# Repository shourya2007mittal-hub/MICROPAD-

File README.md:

# MICROPAD-

I  built a updated macro pad with 9 switches an 0.91 inch Display , a rotor encoder through which I can change between the layers and one RGB LED per switch , It will be  use wireless connection and will use Xiao nrf52840 as the main microcontroller.

## Features

- Base on Xiao NRF Module
- Has per switch LED
- Works wirelessly and has a Battery built in
- Has 9 Switch and 3 Different Layers to switch onto

# Bill of Materials (BOM)

This document contains the list of all components required for the project, including quantities, estimated prices, and direct purchase links.

## Components

| Item | Quantity | Price (USD) | Purchase Link |
|------|----------|------------:|---------------|
| PCB + Shipping | - | 18.72 | https://jlcpcb.com |
| SK6812 Mini-E RGB | 1 Pack | 13.19 | https://www.desertcart.in/products/713547616-50pcs-sk6812-mini-e-rgb-similar-with-ws2812b-sk6812-3228 |
| Mini SPDT Slide Switch (+ Shipping) | Pack of 3 | 1.64 | https://www.amazon.in/gp/product/B0B434R6QF/ref=ox_sc_act_image_1?smid=A2JDRZEGU1IDE2&psc=1 |
| Blank DSA Keycaps | 2 Sets of 5 | 2.00 | https://meckeys.com/shop/accessories/keyboard-accessories/keycaps/blank/blank-dsa-keycaps-1u/ |
| Kailh Hot-Swap Sockets | 2 Packs of 5 | 1.65 | https://meckeys.com/shop/accessories/keyboard-accessories/key-switches/kailh-hot-swap-socket/?attribute_pa_variations=white |
| Gateron Optical Switches | 1 Pack of 10 | 4.50 | https://meckeys.com/shop/accessories/keyboard-accessories/key-switches/gateron-optical-switch-pack/?attribute_pa_key-switches=gateron-optical-silent-brown |
| Meckeys Shipping | - | 1.10 | https://meckeys.com |
| 450mAh 3.7V LiPo Battery | 1 | 1.70 | https://robocraze.com/products/450mah-3-7v-lipo-rechargeable-battery?variant=51440287219936 |
| Rotary Encoder Module | 1 | 0.69 | https://robocraze.com/products/rotary-encoder-module?variant=40193048543385 |
| 0.91" OLED Display Module | 1 | 1.58 | https://robocraze.com/products/0-91-inch-blue-oled-display-module?variant=40194383413401 |
| Seeed Studio XIAO nRF52840 | 1 | 12.16 | https://robocraze.com/products/seeed-studio-xiao-nrf52840-development-board-supports-bluetooth-5-0?variant=47769216516320 |

## Estimated Cost

| Description | Amount (USD) |
|------------|-------------:|
| **Total Estimated Cost** | **58.93** |

### Schematic

###  PCB Design

### 3D Design

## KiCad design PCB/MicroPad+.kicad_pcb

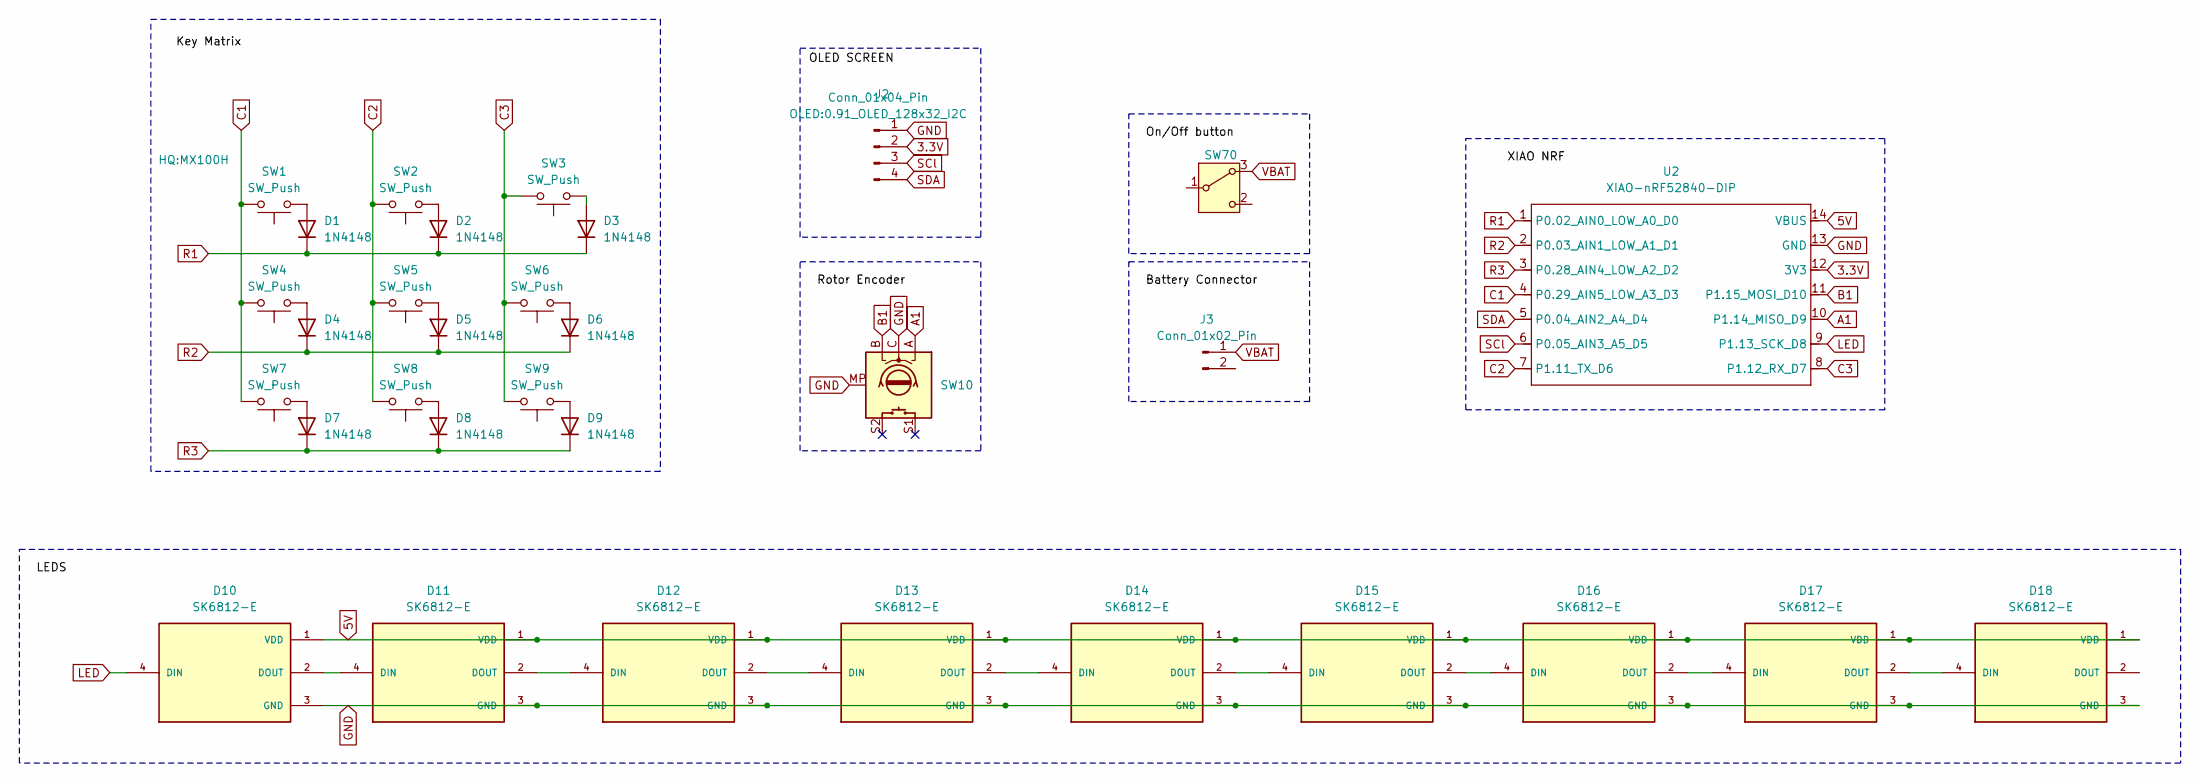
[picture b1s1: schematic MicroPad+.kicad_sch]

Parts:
D1, D2, D3, D4, D5, D6, D7, D8, D9: 1N4148; D_DO-35_SOD27_P7.62mm_Horizontal
D10, D11, D12, D13, D14, D15, D16, D17, D18: SK6812-E; LED_SK6812-E; PARTREV 2
J2: Conn_01x04_Pin; 0.91_OLED_128x32_I2C
J3: Conn_01x02_Pin; AMASS_XT30U-F_1x02_P5.0mm_Vertical
SW1, SW2, SW3, SW4, SW5, SW6, SW7, SW8, SW9: SW_Push; MX100H
SW10: RotaryEncoder_Switch_MP; RotaryEncoder_Alps_EC11E-Switch_Vertical_H20mm
SW70: SW_Wuerth_450301014042; SW_Slide_SPDT_Angled_CK_OS102011MA1Q
U2: XIAO-nRF52840-DIP; XIAO-nRF52840-SMD

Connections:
3.3V: J2.2, U2.12 (3V3)
5V: D10.1 (VDD), D11.1 (VDD), D12.1 (VDD), D13.1 (VDD), D14.1 (VDD), D15.1 (VDD), D16.1 (VDD), D17.1 (VDD), D18.1 (VDD), U2.14 (VBUS)
A1: SW10.A, U2.10 (P1.14_MISO_D9)
B1: SW10.B, U2.11 (P1.15_MOSI_D10)
C1: SW1.2, SW4.2, SW7.2, U2.4 (P0.29_AIN5_LOW_A3_D3)
C2: SW2.2, SW5.2, SW8.2, U2.7 (P1.11_TX_D6)
C3: SW3.2, SW6.2, SW9.2, U2.8 (P1.12_RX_D7)
GND: D10.3 (GND), D11.3 (GND), D12.3 (GND), D13.3 (GND), D14.3 (GND), D15.3 (GND), D16.3 (GND), D17.3 (GND), D18.3 (GND), J2.1, SW10.C, SW10.MP, U2.13 (GND)
LED: D10.4 (DIN), U2.9 (P1.13_SCK_D8)
unnamed: D1.2 (A), SW1.1
unnamed: D2.2 (A), SW2.1
unnamed: D3.2 (A), SW3.1
unnamed: D4.2 (A), SW4.1
unnamed: D5.2 (A), SW5.1
unnamed: D6.2 (A), SW6.1
unnamed: D7.2 (A), SW7.1
unnamed: D8.2 (A), SW8.1
unnamed: D9.2 (A), SW9.1
unnamed: D10.2 (DOUT), D11.4 (DIN)
unnamed: D11.2 (DOUT), D12.4 (DIN)
unnamed: D12.2 (DOUT), D13.4 (DIN)
unnamed: D13.2 (DOUT), D14.4 (DIN)
unnamed: D14.2 (DOUT), D15.4 (DIN)
unnamed: D15.2 (DOUT), D16.4 (DIN)
unnamed: D16.2 (DOUT), D17.4 (DIN)
unnamed: D17.2 (DOUT), D18.4 (DIN)
R1: D1.1 (K), D2.1 (K), D3.1 (K), U2.1 (P0.02_AIN0_LOW_A0_D0)
R2: D4.1 (K), D5.1 (K), D6.1 (K), U2.2 (P0.03_AIN1_LOW_A1_D1)
R3: D7.1 (K), D8.1 (K), D9.1 (K), U2.3 (P0.28_AIN4_LOW_A2_D2)
SCl: J2.3, U2.6 (P0.05_AIN3_A5_D5)
SDA: J2.4, U2.5 (P0.04_AIN2_A4_D4)
VBAT: J3.1, SW70.3 (A)

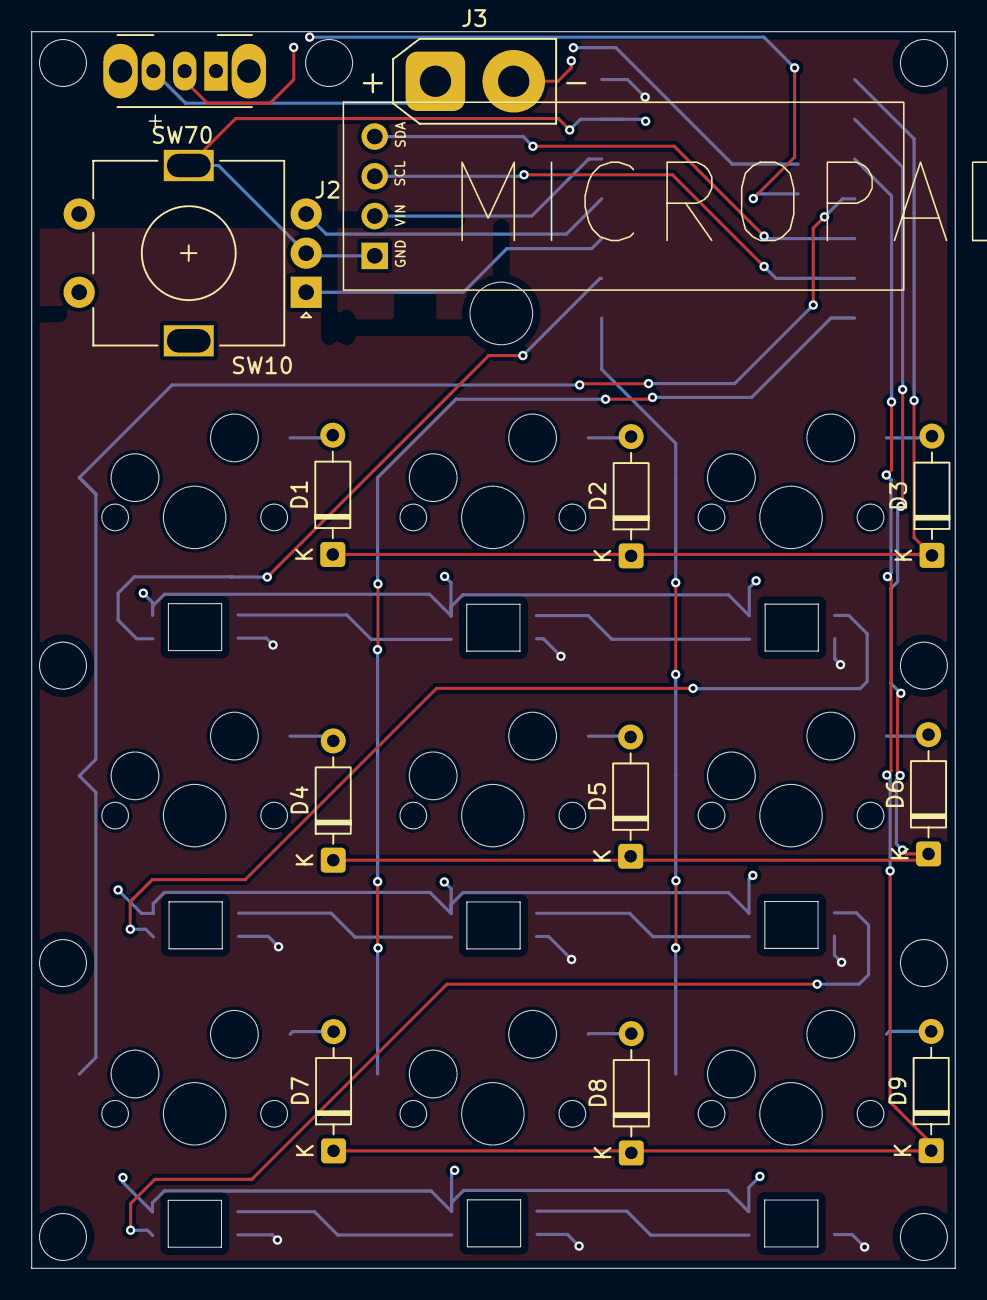
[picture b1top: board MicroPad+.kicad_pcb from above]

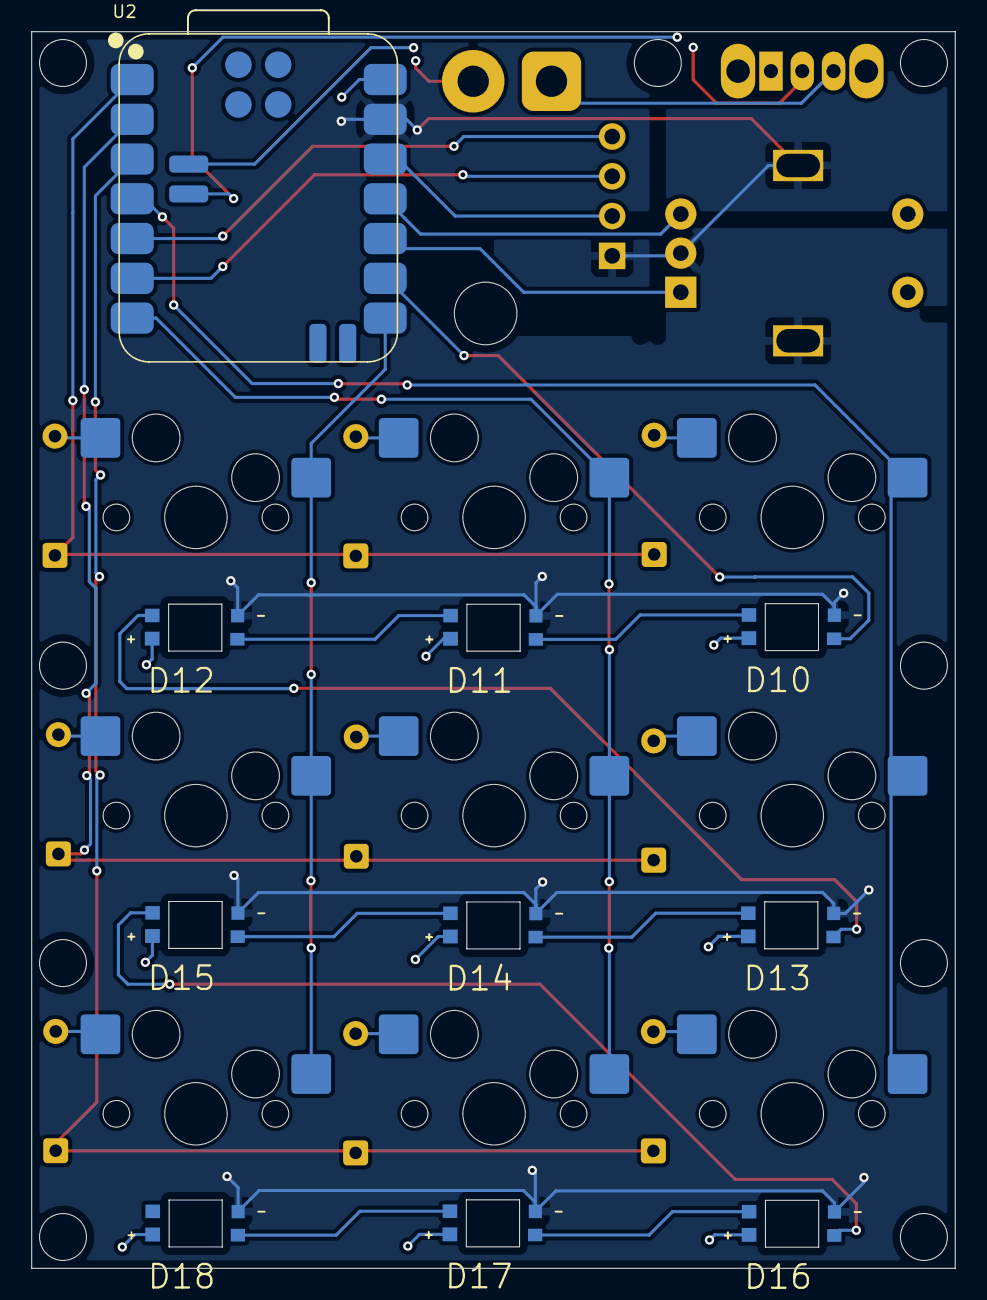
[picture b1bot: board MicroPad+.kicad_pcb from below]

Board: 2 copper layers, 59.0 x 79.0 mm, 32 parts (19 on the bottom side), 32 nets.

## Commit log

2026-06-29 Rename MicroPad_Air1.zip to MicroPad_PLUS.zip
